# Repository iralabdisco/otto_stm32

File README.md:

# Otto

Firmware for Otto's controlboard. Otto is a differential drive robot.

The main program is located in [otto_controller](https://github.com/iralabdisco/otto/tree/master/otto_controller).

## Instructions

If you just want to use the robot you can download the binary file from the [releases](https://github.com/iralabdisco/otto/releases): 

1. Download the lastest otto_controller.bin
2. Plug your Nucleo board in your PC.
3. Copy and paste the .bin file inside your board.

## Coding a driver for otto

You will need to have a way to open a serial port on your PC.

Serial port configuration:

- Baud rate: 115200
- Parity: No
- Stop bit: 1
- Data bits: 8
- Hardware flow control: disabled

1. Before doing anything reset the MCU using the DTR pin in the serial port.
2. The MCU will then wait to receive a ConfigMessage.
3. After the config message is received the PID loop control starts.
4. Every time a VelocityMessage is received Otto will send a StatusMessage.

Refer to [otto_messages.h](https://github.com/iralabdisco/otto_stm32/blob/master/otto_controller/Core/Inc/communication/otto_messages.h) to see how the messages are structured.

The CRC standard used is CRC-32/MPEG-2, tested with python package [crccheck](https://pythonhosted.org/crccheck/crccheck.html)

## Coding style
Follow [Google C++ guideline](https://google.github.io/styleguide/cppguide.html) while working on the project

Eclipse's formatting configuration file can be found [here](https://github.com/google/styleguide/blob/gh-pages/eclipse-cpp-google-style.xml)

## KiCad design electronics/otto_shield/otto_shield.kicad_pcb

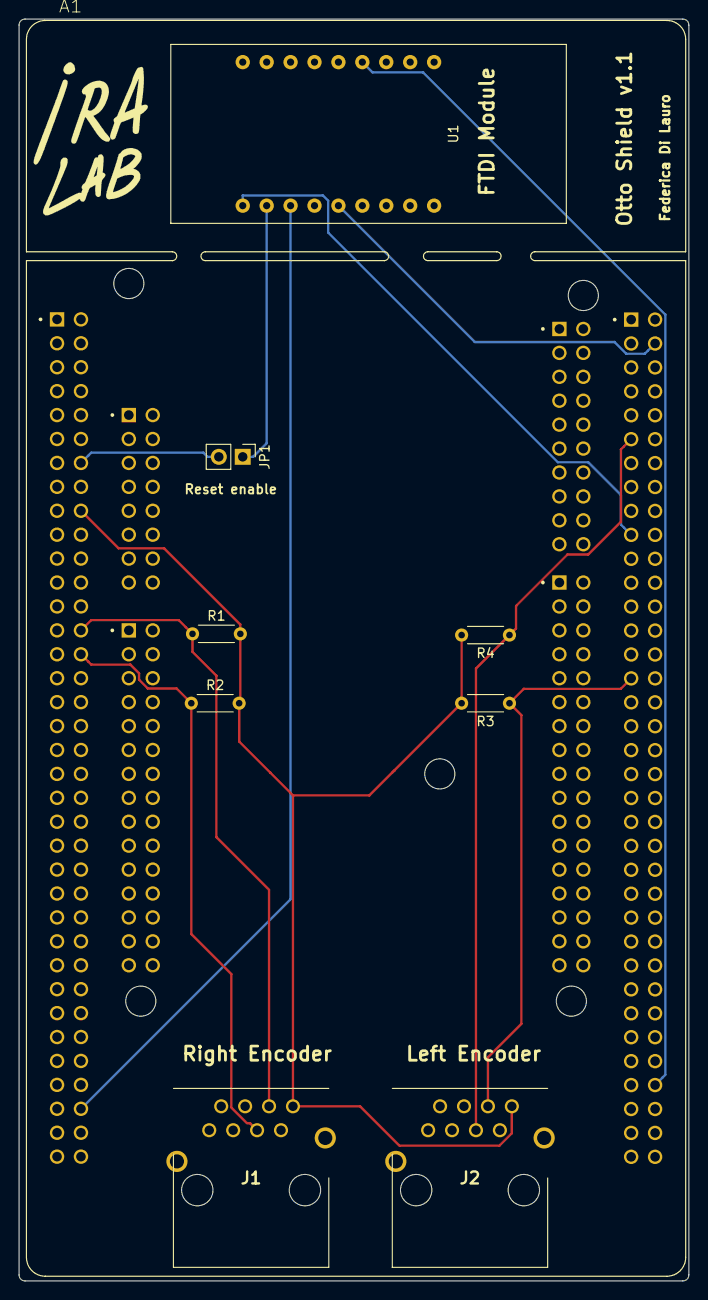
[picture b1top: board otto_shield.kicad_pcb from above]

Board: 2 copper layers, 71.1 x 134.0 mm, 9 parts (0 on the bottom side), 12 nets.

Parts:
A1: NUCLEO-F767ZI; ST_NUCLEO-F767ZI
J1, J2: 3-5338556-1; 353385561
JP1: Jumper; PinHeader_1x02_P2.54mm_Vertical
R1, R2, R3, R4: 2.7K; R_Axial_DIN0204_L3.6mm_D1.6mm_P5.08mm_Horizontal
U1: az_serial_module

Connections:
+5V: A1.CN11_18, J1.1, J2.1, R1.2, R2.2, R3.2, R4.2
/RESET: A1.CN11_14, JP1.2
/TIM2_CH1: A1.CN12_11, J2.4, R4.1
/TIM2_CH2: A1.CN12_31, J2.3, R3.1
/TIM5_CH1: A1.CN11_28, J1.3, R1.1
/TIM5_CH2: A1.CN11_30, J1.4, R2.1
/USART_CTS: A1.CN11_68, U1.16
/USART_RTS: A1.CN12_66, U1.4
/USART_RX: A1.CN12_19, U1.18
/USART_TX: A1.CN12_4, U1.14
GND: A1.CN11_8, A1.CN11_19, A1.CN11_20, A1.CN11_22, A1.CN11_49, A1.CN11_60, A1.CN11_71, A1.CN11_72, A1.CN12_9, A1.CN12_20, A1.CN12_39, A1.CN12_54, A1.CN12_63, A1.CN12_71, A1.CN12_72, J1.2, J1.MH3, J1.MH4, J2.2, J2.MH3, J2.MH4, U1.9, U1.12
unnamed: JP1.1, U1.17

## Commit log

2019-07-26 Starting to learn about drivers, encoders and PID control
2019-07-26 Begin of hardware requirements
2019-08-02 Hardware list is complete
2019-08-02 Starting to setup IDE and libraries
2019-08-02 update ide
2019-08-06 moved files to wiki
2019-09-03 test encoder working
2019-09-03 pwm first test
2019-09-03 add gitignore
2019-09-06 pwm function
2019-09-09 cpp not working
2019-09-09 cpp works
2019-09-11 config periferiche okok, da sistemare STM32Hardware.h
2019-09-11 hello world! funziona
2019-09-11 publisher funziona, subscriber no
2019-09-12 subscriber funziona
2019-09-19 clean
2019-09-19 initialize project
2019-09-19 add c++ style guide
2019-09-19 fix link
2019-09-19 encoder not compiling
2019-09-20 encoder tick reading and reset (working)
2019-09-26 Start working on timer callback
2019-10-08 start reading velocity from encoder
2019-10-08 ticks to linear velocity
2019-10-09 encoder reading
2019-10-15 begin managing directioN
2019-10-15 fix counter backward direction
2019-10-16 update to new firmware version broke the encoder readings
2019-10-16 encoder resolution x2
2019-10-18 Reading velocity fixes, everything works now
2019-10-18 Start odometry
2019-10-23 odometry
2019-11-18 rosserial works, odometry si rompe
2019-11-22 rosserial works, testing odometry
2019-12-02 add python script to receive from UART
2019-12-02 goodbye rosserial
2019-12-02 fix formatting
2019-12-03 serial transmission
2019-12-03 specify endianness
2019-12-06 uart tests
2019-12-06 split python script, otto can receive now
2019-12-06 receive and trasmit work together
2019-12-13 configure pins
2019-12-14 pid and motor_controller classes implemented
2019-12-14 pid control, to be tested
2019-12-15 fix interrupt prioriies
2019-12-15 fix communication for testing
2019-12-17 pid works, needs tuning
2019-12-17 pid derviative term
2019-12-18 pid: log dutycycle->velocity for matlab
2019-12-18 add custom name to log file
2020-01-20 move tools in a directory
2020-01-20 organize code and folders
2020-01-20 swap left/right in pid_tuning
2020-01-20 test submodule
2020-01-20 fix #7
2020-01-22 fix pid, remove antiwindup, start code refactoring
2020-01-22 refactor pid
2020-01-23 fix motor_controller
2020-01-23 start ticks calibration, now otto can be driven with joystick!
2020-01-24 add ticks calibration tests and results
2020-01-27 organize folders
2020-01-27 update otto_controller and pid_tuning with new ticks calibration
2020-01-27 remove submodules
2020-01-27 clean repo
2020-01-28 fix catkin_ws
2020-01-28 fix python scripts, now looping till we can open serial port
2020-01-29 fix pid_tuning
2020-01-29 remove ticks_logger, encoders get the meters from wheel circumference (now measured accurately)
2020-02-04 move encoder.cpp to encoder.h
2020-02-04 remove encoder.cpp
2020-02-04 remove autogenerated files and add rule to gitignore
2020-02-04 remove autogenerated files
2020-02-04 remove eclipse files
2020-02-04 modify gitignore
2020-02-04 separate peripherals init from main
2020-02-04 remove autogen files
2020-02-04 remove #define constants
2020-02-06 clean utils folder
2020-02-06 remove ros build files
2020-02-06 re-add linker script because they are not regenerated by stm32cube
2020-02-06 remove test
2020-02-06 separate peripheral init
2020-02-06 move encoder methods to header file
2020-02-06 remove launch files (autogenerated)
2020-02-06 remove constants.h
2020-02-06 remove protocol buffers test
2020-02-06 remove old matlab
2020-02-06 remove ros workspace files
2020-02-06 remove proto-test
2020-02-06 remove eclipse file
2020-02-06 add ros launcher for dario's joypad
2020-02-06 remove compiled files
2020-02-07 add pid anti windup to pid_tuning
2020-02-07 add pid antiwindup to otto_controller
2020-02-07 update pid_tuning classes
2020-02-07 add protobuf messages definitions, python and C code
2020-02-10 opening serial in non-exclusive mode works
2020-02-10 dma tests
2020-02-11 switch to protobuf v2
2020-02-11 dma works
2020-02-11 otto protobuf test works
2020-02-11 receiving velocities command using protobuf
2020-02-12 receive cmd_vel and send velocity with protobuf
2020-02-12 change transmission frequency to 10Hz
2020-02-25 change uart baud rate to 9600
2020-02-25 change status field in StatusMessage to fixed size
2020-02-25 update proto messages
2020-02-25 move classes to subfolder
2020-02-25 organize subfolders
2020-02-25 move serial transmission scripts to new package
2020-02-25 create roslaunch file for serial bridge
2020-02-25 move launch files to new subdirectory
2020-02-25 update launch files
2020-02-25 invert joypad x
2020-02-25 remove pyserial examples
2020-03-02 print debug messages
2020-03-02 fix odometry
2020-03-02 separate serial_bridge from other launch files
2020-03-02 add fault interrupts, fix #6
2020-03-04 add hardware flow control for computer->st transmission
2020-03-06 add pcb #30
2020-03-09 change rj45 connector to shielded rj45
2020-03-09 remove temporary kicad files
2020-03-10 add kicad autogenerated files to gitignore
2020-03-12 fix rx bug
2020-03-15 remove throttle node, computer->st transmission works without it
2020-03-15 fix communication bug
2020-03-15 reset mcu from serial adapter
2020-03-15 include serial_bridge.launch in other launch files
2020-03-15 add connection from the serial module to allow reset
2020-03-23 fix missing import
2020-04-14 fix odometry error when going straight
2020-04-14 update gitignore
2020-04-14 clean code
2020-04-14 fix style
2020-04-14 remove serial nodes
2020-04-14 add serial node which is both transmitter and receiver
2020-04-14 fix joypad signs
2020-04-14 fix gitignore
2020-04-14 modify ros launch files to use new serial node
2020-04-14 fix joypad.launch
2020-05-12 log pololu fault python fix #43
2020-05-12 reset st on rospy shutdown, fix #42
2020-07-22 odometry bug fix, close #46
2021-08-05 synchronous communication, remove protobuf
2021-08-06 accumulate ticks to send
2021-08-06 receive config parameters at startup, close #13
2021-08-06 file cleanup
2021-08-06 README.md
2021-08-09 fix ticks type
2021-08-10 New communication system (#49)
    * synchronous communication, remove protobuf
    * accumulate ticks to send
    * receive config parameters at startup, close #13
    * file cleanup
    * README.md
    * fix ticks type
2021-10-13 Jack release (#50)
    * synchronous communication, remove protobuf
    * accumulate ticks to send
    * receive config parameters at startup, close #13
    * file cleanup
    * README.md
    * fix ticks type
2024-06-17 aggiunto sistema di sicurezza in caso di non risposta dell'encoder
2024-06-24 aggiunta adc
2024-07-17 aggiunto controllo corrente
2024-07-17 aggiunto adc_counter
2024-10-16 tolto while(1)
